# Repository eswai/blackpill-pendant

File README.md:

# Modulo architecture Blackpill pendant

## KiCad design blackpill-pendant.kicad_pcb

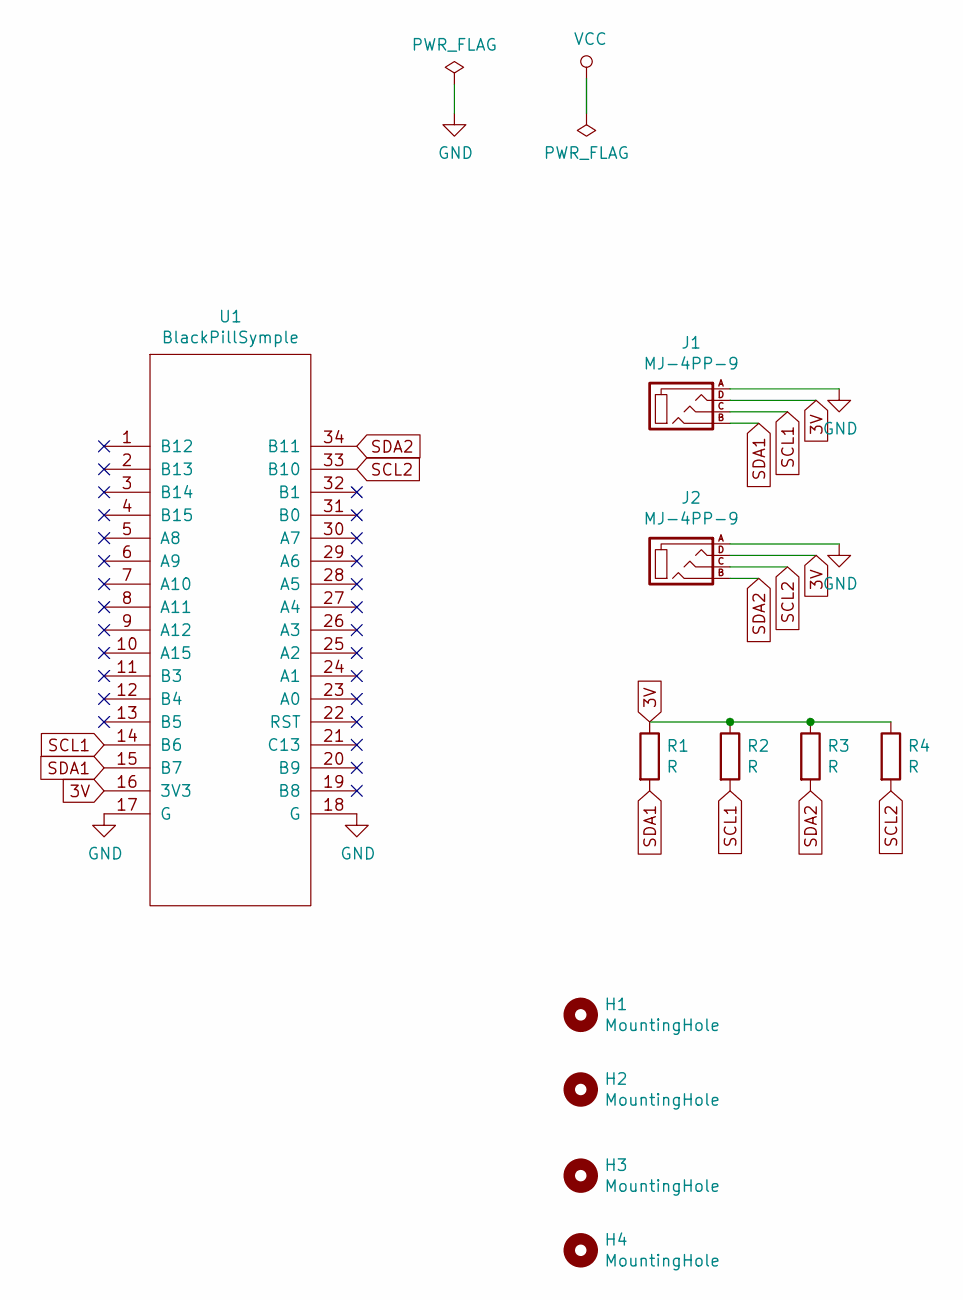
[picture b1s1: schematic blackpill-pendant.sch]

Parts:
H1, H2, H3, H4: MountingHole; MountingHole_3.5mm
J1, J2: MJ-4PP-9
R1, R2, R3, R4: R; R_0603_1608Metric_Pad1.05x0.95mm_HandSolder
U1: BlackPillSymple; BlackPillSimple

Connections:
3V: J1.D, J2.D, R1.1, R2.1, R3.1, R4.1, U1.16 (3V3)
GND: J1.A, J2.A, U1.17 (G), U1.18 (G)
SCL1: J1.C, R2.2, U1.14 (B6)
SCL2: J2.C, R4.2, U1.33 (B10)
SDA1: J1.B, R1.2, U1.15 (B7)
SDA2: J2.B, R3.2, U1.34 (B11)

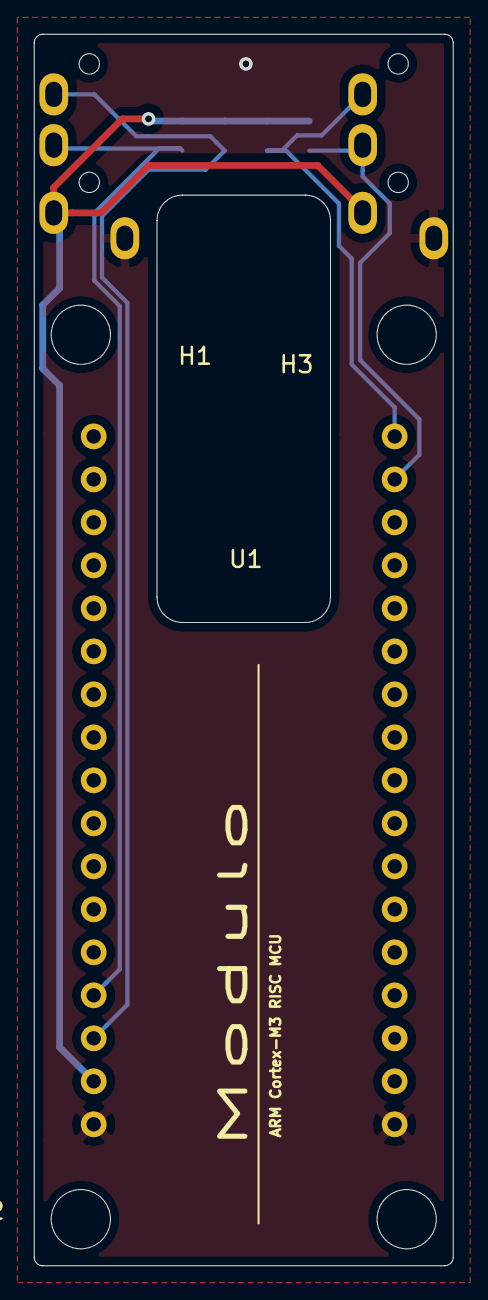
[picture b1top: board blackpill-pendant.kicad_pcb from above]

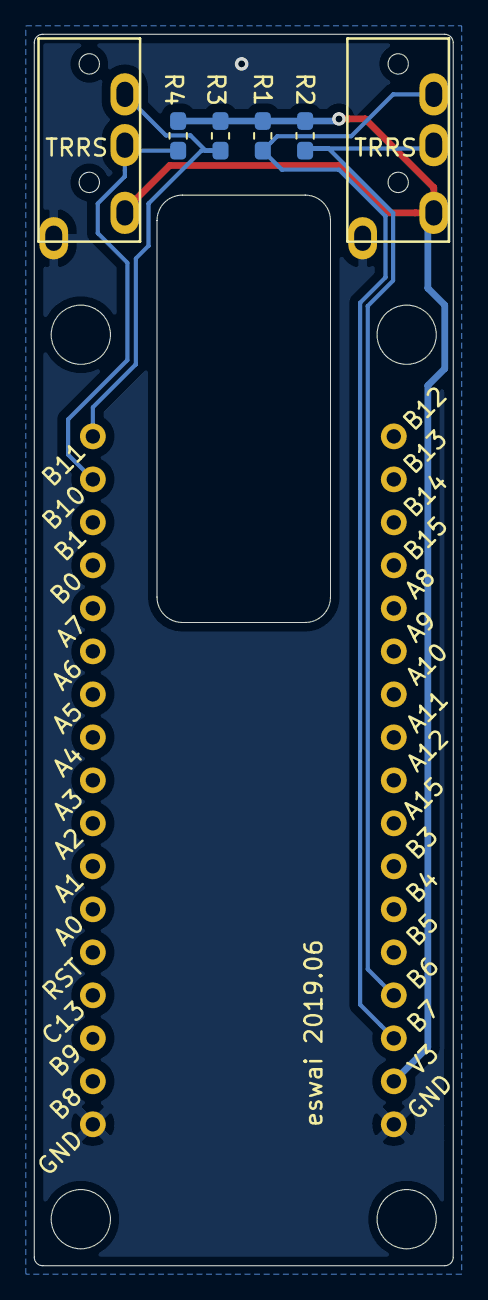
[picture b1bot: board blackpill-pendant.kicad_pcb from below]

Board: 2 copper layers, 24.8 x 72.8 mm, 11 parts (6 on the bottom side), 6 nets.

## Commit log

2019-06-30 Photos
